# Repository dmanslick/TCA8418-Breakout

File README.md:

KiCAD stuff for a TCA8418 breakout

TCA8418 Datasheet: <https://www.ti.com/lit/ds/symlink/tca8418.pdf>

Thermal pad not needing to be connected: <https://e2e.ti.com/support/interface-group/interface/f/interface-forum/723332/tca8418-thermal-pad-connection>

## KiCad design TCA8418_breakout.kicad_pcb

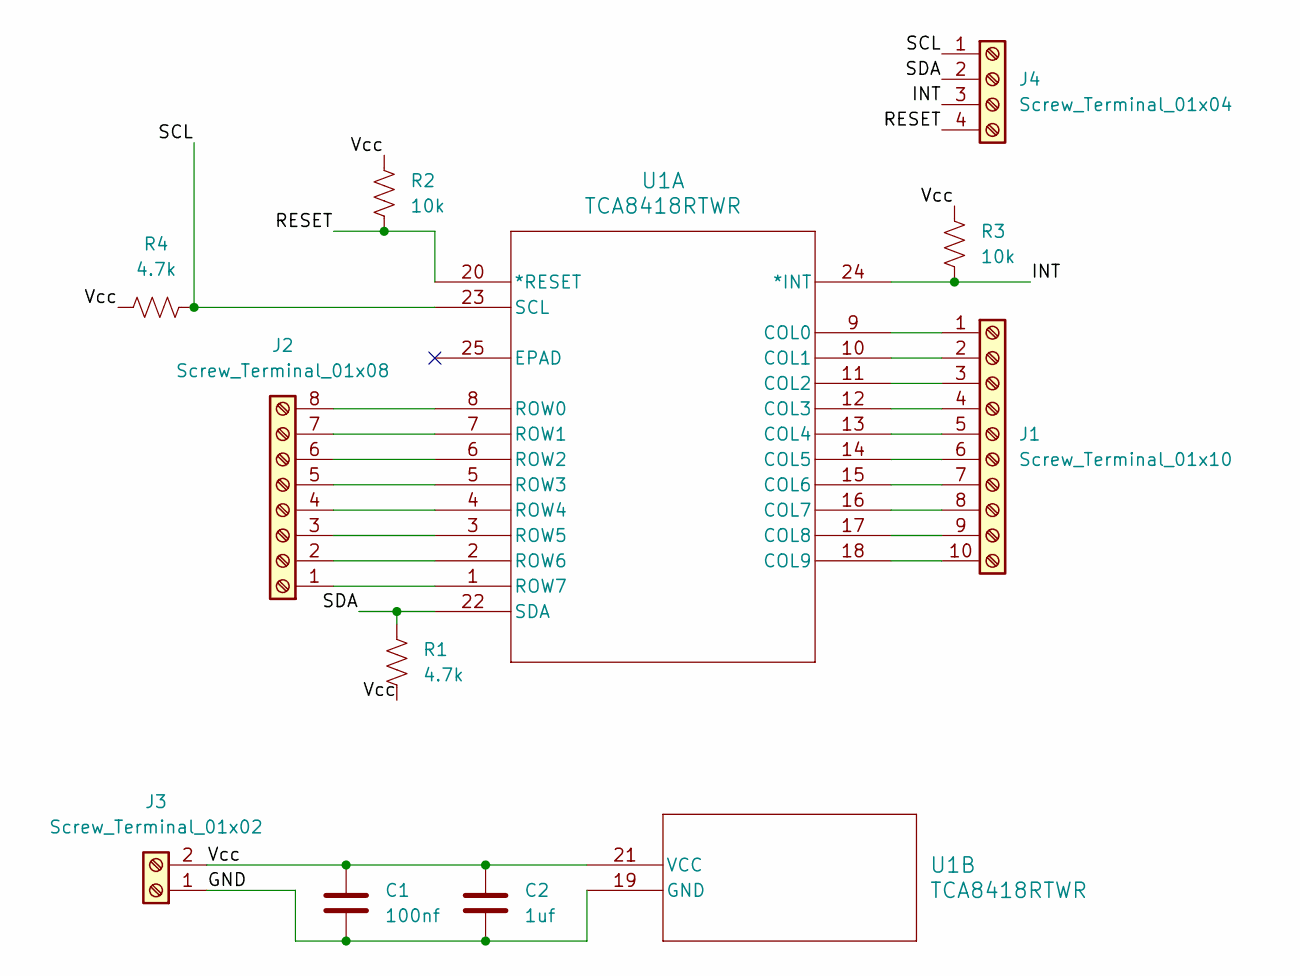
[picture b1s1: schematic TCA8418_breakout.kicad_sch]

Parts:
C1: 100nf; C_0603_1608Metric
C2: 1uf; C_0603_1608Metric
J1: Screw_Terminal_01x10; TerminalBlock_TE_1-282834-0_1x10_P2.54mm_Horizontal
J2: Screw_Terminal_01x08; TerminalBlock_TE_282834-8_1x08_P2.54mm_Horizontal
J3: Screw_Terminal_01x02; TerminalBlock_TE_282834-2_1x02_P2.54mm_Horizontal
J4: Screw_Terminal_01x04; TerminalBlock_TE_282834-4_1x04_P2.54mm_Horizontal
R1, R4: 4.7k; R_0603_1608Metric
R2, R3: 10k; R_0603_1608Metric
U1: TCA8418RTWR; RTW24_2P45X2P45

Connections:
/GND: C1.2, C2.2, J3.1, U1.19 (GND)
/INT: J4.3, R3.2, U1.24 (*INT)
/RESET: J4.4, R2.2, U1.20 (*RESET)
/SCL: J4.1, R4.2, U1.23 (SCL)
/SDA: J4.2, R1.1, U1.22 (SDA)
/Vcc: C1.1, C2.1, J3.2, R1.2, R2.1, R3.1, R4.1, U1.21 (VCC)
unnamed: J1.1, U1.9 (COL0)
unnamed: J1.2, U1.10 (COL1)
unnamed: J1.3, U1.11 (COL2)
unnamed: J1.4, U1.12 (COL3)
unnamed: J1.5, U1.13 (COL4)
unnamed: J1.6, U1.14 (COL5)
unnamed: J1.7, U1.15 (COL6)
unnamed: J1.8, U1.16 (COL7)
unnamed: J1.9, U1.17 (COL8)
unnamed: J1.10, U1.18 (COL9)
unnamed: J2.1, U1.1 (ROW7)
unnamed: J2.2, U1.2 (ROW6)
unnamed: J2.3, U1.3 (ROW5)
unnamed: J2.4, U1.4 (ROW4)
unnamed: J2.5, U1.5 (ROW3)
unnamed: J2.6, U1.6 (ROW2)
unnamed: J2.7, U1.7 (ROW1)
unnamed: J2.8, U1.8 (ROW0)

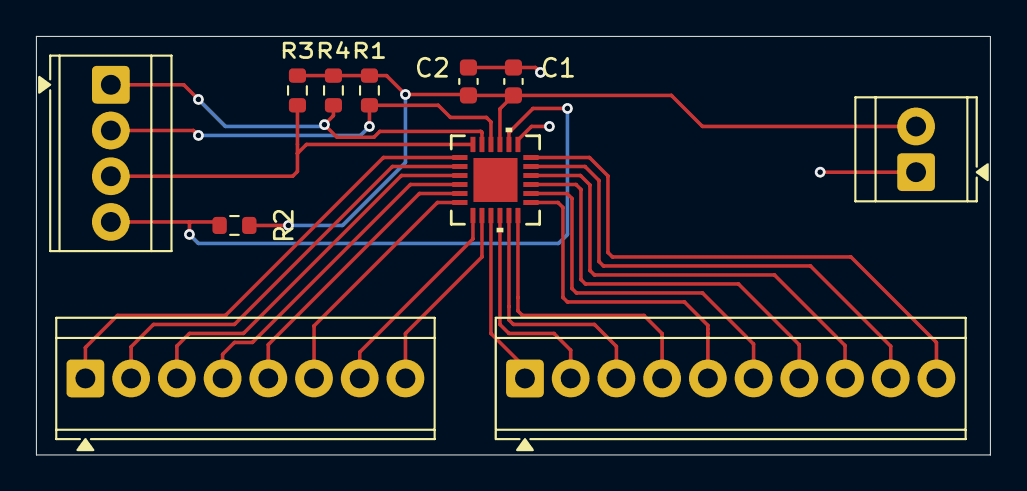
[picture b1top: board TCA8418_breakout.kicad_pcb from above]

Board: 2 copper layers, 53.0 x 23.2 mm, 11 parts (0 on the bottom side), 24 nets.
